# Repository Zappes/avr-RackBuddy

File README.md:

Der RackBuddy
============

Was isses?
-------------

Der RackBuddy ist ein Dingsbums für mein Serverrack, das Temperaturen misst, sie auf 7-Segment-Anzeigen ausgibt und per USB an den Rechner meldet.

Zum RackBuddy gibt es auch ein paar Videos, und zwar hier:

 - [Playlist bei Youtube](http://www.youtube.com/playlist?list=PLFFlJlvZ--PkYDAD19FQtcRBbY8yCnrR-)

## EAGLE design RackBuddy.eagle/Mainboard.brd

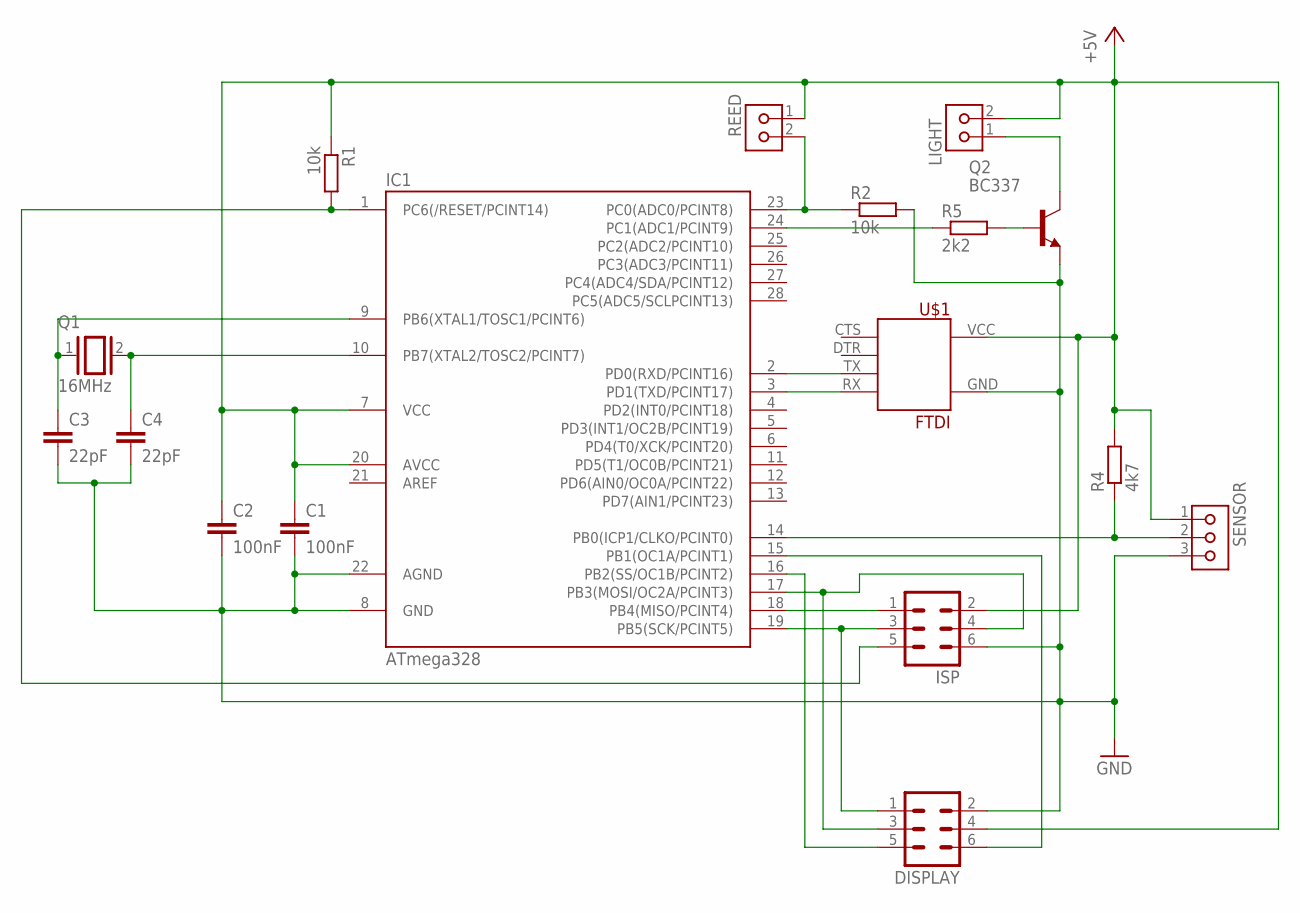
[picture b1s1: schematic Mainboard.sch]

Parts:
C1: 100nF; C050-025X075
C2: 100nF; C025-025X050
C3, C4: 22pF; C025-025X050
DISPLAY: ML6
IC1: ATmega328; DIL28-3
ISP: ML6
LIGHT: KK2VSQ; KK-V-2-SQ
Q1: 16MHz; QS
Q2: BC337; TO92-STRAIGHT-0.254
R1: 10k; 0207/10
R2: 10k; 0204V
R4: 4k7; 0204/7
R5: 2k2; 0204/7
REED: KK2VSQ; KK-V-2-SQ
SENSOR: KK3V; KK-V-3
U$1: FTDI; FTDI-1

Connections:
+5V: C1.1, C2.1, DISPLAY.4, IC1.7 (VCC), IC1.20 (AVCC), ISP.2, LIGHT.2, R1.1, R4.2, REED.1, SENSOR.1, U$1.VCC (+5V)
GND: C1.2, C2.2, C3.2, C4.2, DISPLAY.2, IC1.8 (GND), IC1.22 (AGND), ISP.6, Q2.3 (E), R2.2, SENSOR.3, U$1.GND
unnamed: Q2.2 (B), R5.2
unnamed: IC1.24 (PC1(ADC1/PCINT9)), R5.1
unnamed: IC1.2 (PD0(RXD/PCINT16)), U$1.TX
unnamed: IC1.3 (PD1(TXD/PCINT17)), U$1.RX
unnamed: C3.1, IC1.9 (PB6(XTAL1/TOSC1/PCINT6)), Q1.1
unnamed: C4.1, IC1.10 (PB7(XTAL2/TOSC2/PCINT7)), Q1.2
unnamed: DISPLAY.3, IC1.17 (PB3(MOSI/OC2A/PCINT3)), ISP.4
unnamed: IC1.1 (PC6(/RESET/PCINT14)), ISP.5, R1.2
unnamed: IC1.23 (PC0(ADC0/PCINT8)), R2.1, REED.2
unnamed: IC1.14 (PB0(ICP1/CLKO/PCINT0)), R4.1, SENSOR.2
unnamed: LIGHT.1, Q2.1 (C)
unnamed: DISPLAY.5, IC1.16 (PB2(SS/OC1B/PCINT2))
unnamed: IC1.18 (PB4(MISO/PCINT4)), ISP.1
unnamed: DISPLAY.1, IC1.19 (PB5(SCK/PCINT5)), ISP.3
unnamed: DISPLAY.6, IC1.15 (PB1(OC1A/PCINT1))

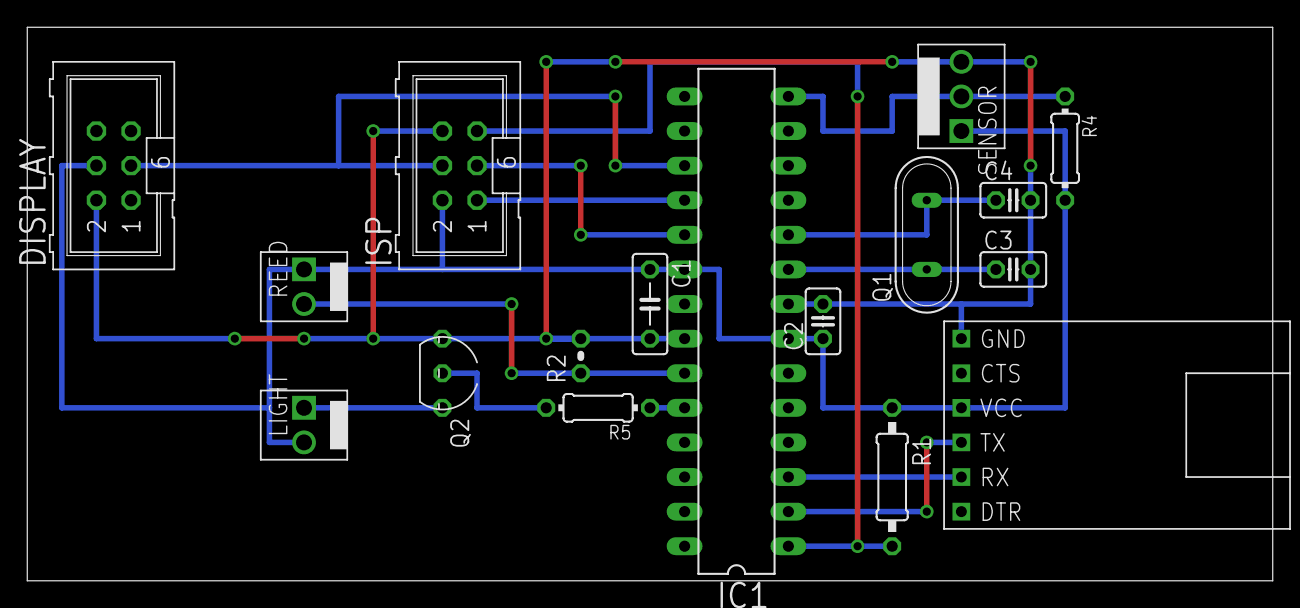
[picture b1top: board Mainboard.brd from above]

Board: 3 copper layers, 91.4 x 40.6 mm, 17 parts (0 on the bottom side), 17 nets.

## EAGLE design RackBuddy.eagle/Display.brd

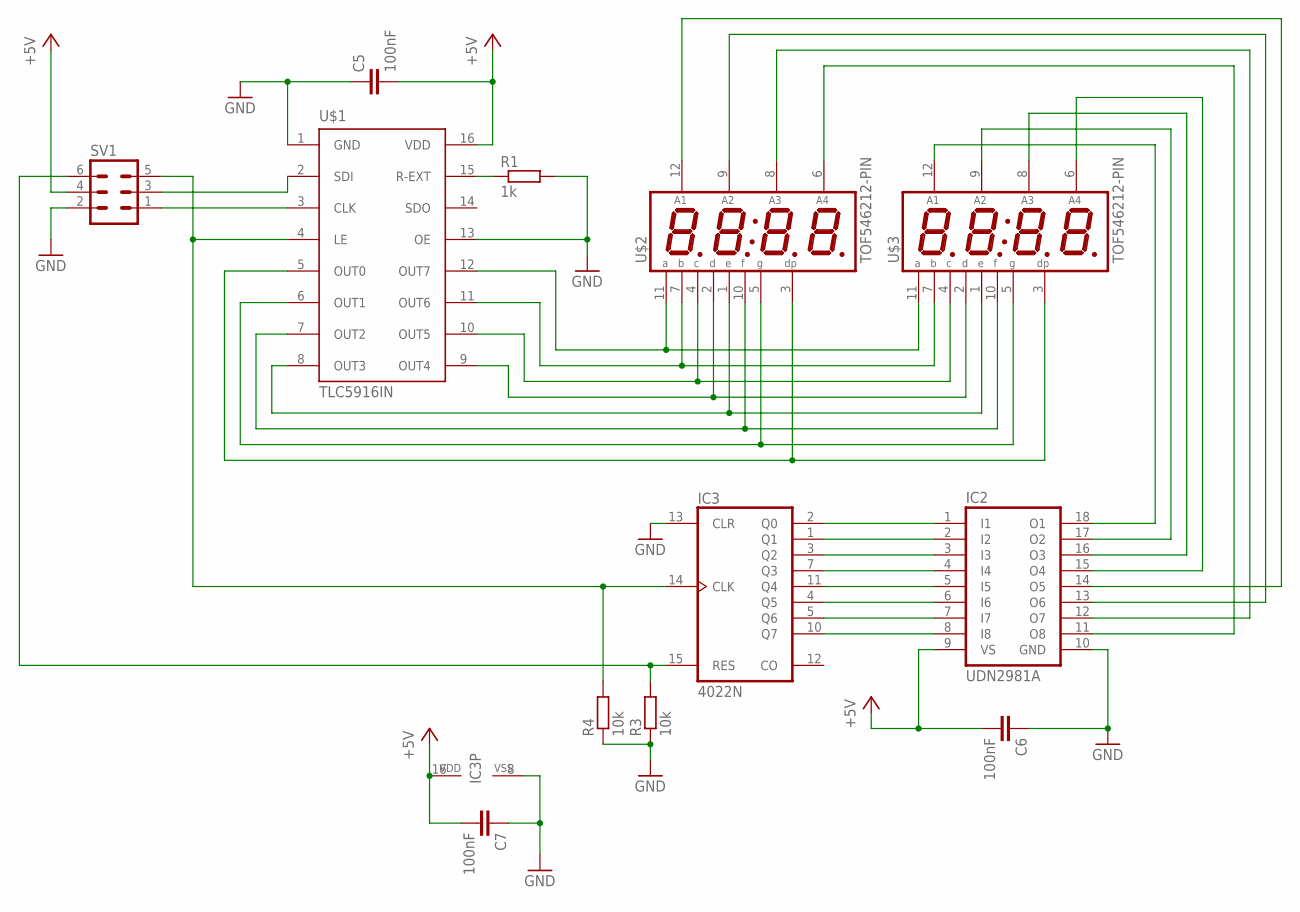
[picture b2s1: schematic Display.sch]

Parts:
C5, C6, C7: 100nF; C025-024X044
IC2: UDN2981A; DIL18
IC3: 4022N; DIL16
R1: 1k; 0204/7
R3, R4: 10k; 0204V
SV1: ML6L
U$1: TLC5916IN; DIL16
U$2, U$3: TOF546212-PIN; TOF5462*

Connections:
+5V: C5.2, C6.2, C7.2, IC2.9 (VS), IC3.16 (VDD), SV1.4, U$1.16 (VDD)
CLOCK: SV1.1, U$1.3 (CLK)
DATA: SV1.3, U$1.2 (SDI)
GND: C5.1, C6.1, C7.1, IC2.10 (GND), IC3.8 (VSS), IC3.13 (CLR), R1.2, R3.1, R4.1, SV1.2, U$1.1 (GND), U$1.13 (OE)
LATCH: IC3.14 (CLK), R4.2, SV1.5, U$1.4 (LE)
unnamed: U$1.11 (OUT6), U$2.7 (B), U$3.7 (B)
unnamed: IC2.17 (O2), U$3.9 (A2)
unnamed: U$1.10 (OUT5), U$2.4 (C), U$3.4 (C)
unnamed: U$1.9 (OUT4), U$2.2 (D), U$3.2 (D)
unnamed: R1.1, U$1.15 (R-EXT)
unnamed: U$1.8 (OUT3), U$2.1 (E), U$3.1 (E)
unnamed: U$1.7 (OUT2), U$2.10 (F), U$3.10 (F)
unnamed: U$1.6 (OUT1), U$2.5 (G), U$3.5 (G)
unnamed: U$1.5 (OUT0), U$2.3 (DP), U$3.3 (DP)
unnamed: IC2.1 (I1), IC3.2 (Q0)
unnamed: IC2.2 (I2), IC3.1 (Q1)
unnamed: IC2.3 (I3), IC3.3 (Q2)
unnamed: IC2.4 (I4), IC3.7 (Q3)
unnamed: IC2.5 (I5), IC3.11 (Q4)
unnamed: IC2.6 (I6), IC3.4 (Q5)
unnamed: IC2.7 (I7), IC3.5 (Q6)
unnamed: IC2.8 (I8), IC3.10 (Q7)
unnamed: IC2.18 (O1), U$3.12 (A1)
unnamed: IC2.14 (O5), U$2.12 (A1)
unnamed: U$1.12 (OUT7), U$2.11 (A), U$3.11 (A)
unnamed: IC2.13 (O6), U$2.9 (A2)
unnamed: IC2.16 (O3), U$3.8 (A3)
unnamed: IC2.12 (O7), U$2.8 (A3)
unnamed: IC2.15 (O4), U$3.6 (A4)
unnamed: IC2.11 (O8), U$2.6 (A4)
RESET: IC3.15 (RES), R3.2, SV1.6

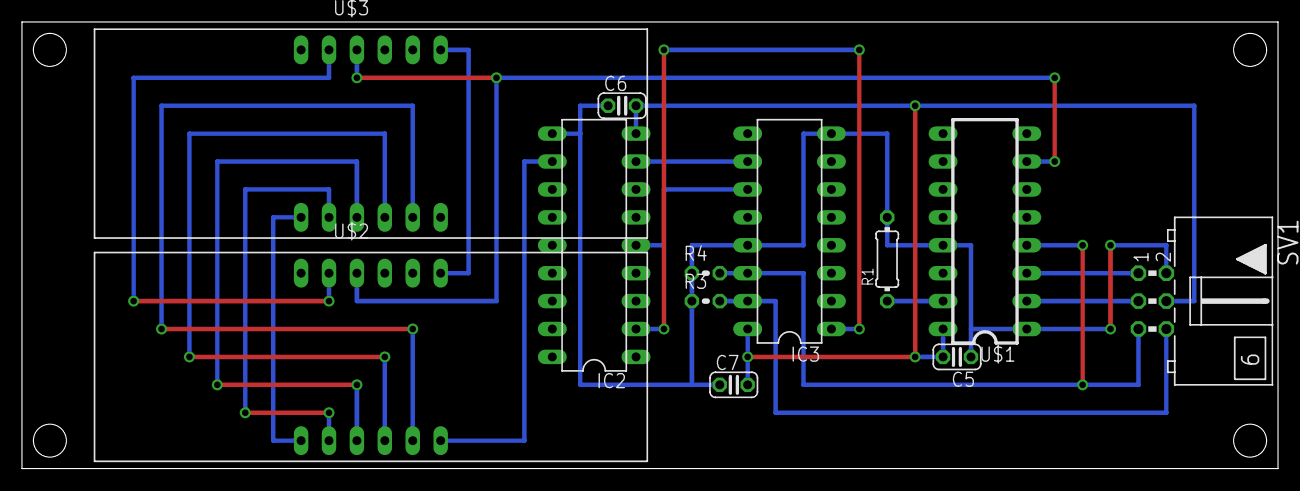
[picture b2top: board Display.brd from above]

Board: 2 copper layers, 114.3 x 40.6 mm, 12 parts (0 on the bottom side), 31 nets.

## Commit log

2014-11-09 Added libs
2014-11-18 Added README
2014-11-18 Added stuff, updated .gitignore
2014-11-24 Added door light and schematics
2014-12-03 An den Plänen gearbeitet
